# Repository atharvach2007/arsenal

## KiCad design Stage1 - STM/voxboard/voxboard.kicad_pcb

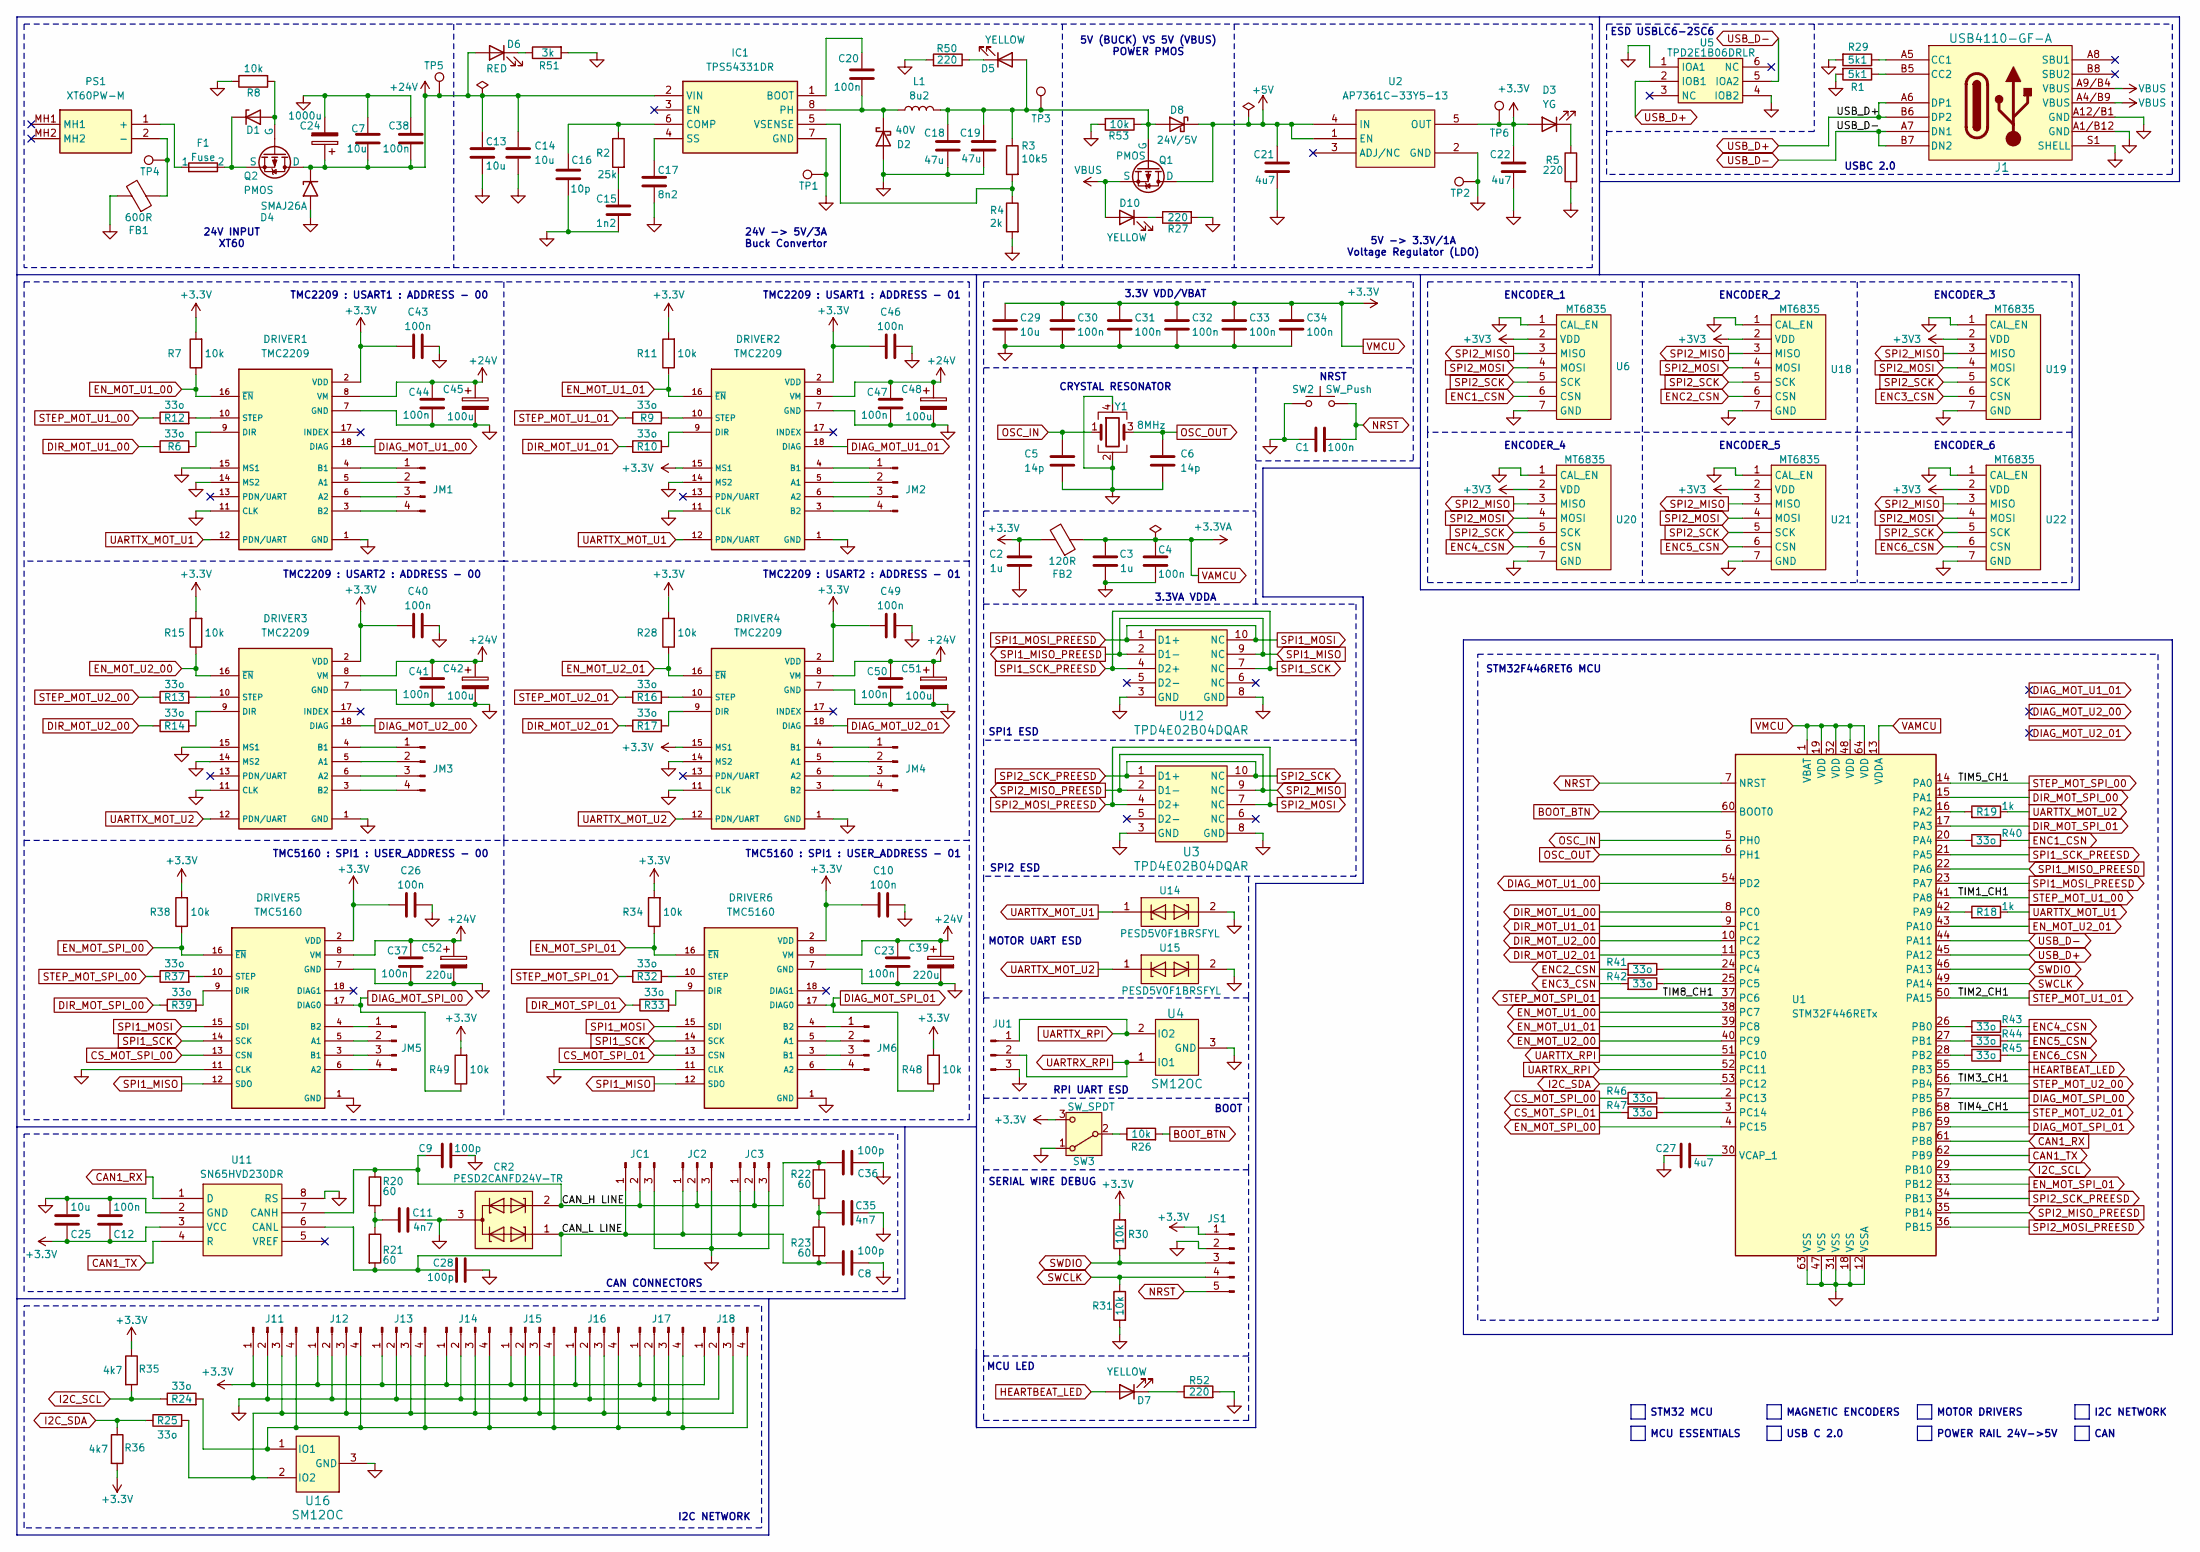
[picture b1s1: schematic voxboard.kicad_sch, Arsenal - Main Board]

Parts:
C1, C4, C10, C12, C23, C26, C30, C31, C32, C33, C34, C37, C38, C40, C41, C43, C44, C46, C47, C49, C50: 100n; C_0402_1005Metric
C2, C3: 1u; C_0603_1608Metric
C5, C6: 14p; C_0402_1005Metric
C7, C25, C29: 10u; C_0603_1608Metric
C8, C9, C28, C36: 100p; C_0402_1005Metric
C11, C35: 4n7; C_0402_1005Metric
C13, C14: 10u; C_1210_3225Metric
C15: 1n2; C_0805_2012Metric
C16: 10p; C_0805_2012Metric
C17: 8n2; C_0201_0603Metric
C18, C19: 47u; C_1210_3225Metric
C20: 100n; C_0805_2012Metric
C21, C22, C27: 4u7; C_0603_1608Metric
C24: 1000u; CP_Radial_D8.0mm_P3.50mm
C39, C52: 220u; CP_Radial_D10.0mm_P5.00mm
C42, C45, C48, C51: 100u; CP_Radial_D8.0mm_P3.50mm
CR2: PESD2CANFD24V-TR; SOT-23
D1: D_Zener; D_SOD-123
D2: 40V; D_SMA
D3: YG; LED_0603_1608Metric
D4: SMAJ26A; D_SMA
D5, D10: YELLOW; LED_0603_1608Metric
D6: RED; LED_0603_1608Metric
D7: YELLOW; LED_0805_2012Metric
D8: 24V/5V; D_SMC
DRIVER1, DRIVER2, DRIVER3, DRIVER4: TMC2209; MODULE_TMC2209_5160
DRIVER5, DRIVER6: TMC5160; MODULE_TMC2209_5160
F1: Fuse; CONN_3557-2_KEY
FB1: 600R; L_1210_3225Metric
FB2: 120R; L_0603_1608Metric
IC1: TPS54331DR; SOIC-8_3.9x4.9mm_P1.27mm
J1: USB4110-GF-A; USB_C_Receptacle_GCT_USB4110
J11, J12, J13, J14, J15, J16, J17, J18: Conn_01x04_Pin; JST_GH_BM04B-GHS-TBT_1x04-1MP_P1.25mm_Vertical
JC1, JC2, JC3: Conn_01x03_Pin; JST_GH_BM03B-GHS-TBT_1x03-1MP_P1.25mm_Vertical
JM1, JM2, JM3, JM4, JM5, JM6: Conn_01x04_Pin; JST_VH_B4P-VH-FB-B_1x04_P3.96mm_Vertical
JS1: Conn_01x05_Pin; PinHeader_1x05_P2.54mm_Vertical
JU1: Conn_01x03_Pin; PinHeader_1x03_P2.54mm_Vertical
L1: 8u2; L_KOHERELEC_MDA7050_7.3x6.6mm
PS1: XT60PW-M; AMASS_XT60PW-M_1x02_P7.20mm_Horizontal
Q1: PMOS; SOT-23
Q2: PMOS; TO-252-2
R1, R29: 5k1; R_0402_1005Metric
R2: 25k; R_0402_1005Metric
R3: 10k5; R_0402_1005Metric
R4: 2k; R_0402_1005Metric
R5, R27, R50, R52: 220; R_0402_1005Metric
R6, R9, R10, R12, R13, R14, R16, R17, R24, R25, R32, R33, R37, R39, R40, R41, R42, R43, R44, R45, R46, R47: 33o; R_0402_1005Metric
R7, R8, R11, R15, R26, R28, R30, R31, R34, R38, R48, R49, R53: 10k; R_0402_1005Metric
R18, R19: 1k; R_0402_1005Metric
R20, R21, R22, R23: 60; R_0603_1608Metric
R35, R36: 4k7; R_0402_1005Metric
R51: 3k; R_0402_1005Metric
SW2: SW_Push; SW_PUSH_B3U-1000PM
SW3: SW_SPDT; SW_SPDT_PCM12
TP1, TP2, TP4: TestPoint; TestPoint_Pad_2.0x2.0mm
TP3, TP5, TP6: TestPoint; TestPoint_Pad_D2.0mm
U1: STM32F446RETx; LQFP64-10x10mm
U2: AP7361C-33Y5-13; AP7361C-33Y5-13_SOT89-5_DIO
U3, U12: TPD4E02B04DQAR; USON-10_2.5x1.0mm_P0.5mm
U4, U16: SM12OC; SOT-23
U5: TPD2E1B06DRLR; SOT-666
U6, U18, U19, U20, U21, U22: MT6835; JST_GH_BM07B-GHS-TBT_1x07-1MP_P1.25mm_Vertical
U11: SN65HVD230DR; SOIC-8_3.9x4.9mm_P1.27mm
U14, U15: PESD5V0F1BRSFYL; Nexperia_DSN0603-2_0.6x0.3mm_P0.4mm
Y1: 8MHz; Crystal_SMD_3225-4Pin_3.2x2.5mm

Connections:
+3V3: U6.2 (VDD), U18.2 (VDD), U19.2 (VDD), U20.2 (VDD), U21.2 (VDD), U22.2 (VDD)
+5V: C21.1, D8.1 (K), Q1.1 (D), U2.1 (EN), U2.4 (IN)
+24V: C7.2, C13.1, C14.1, C23.1, C24.1, C37.1, C38.2, C39.1, C41.1, C42.1, C44.1, C45.1, C47.1, C48.1, C50.1, C51.1, C52.1, D4.1 (A1), D6.2 (A), DRIVER1.8 (VM), DRIVER2.8 (VM), DRIVER3.8 (VM), DRIVER4.8 (VM), DRIVER5.8 (VM), DRIVER6.8 (VM), IC1.2 (VIN), Q2.1 (D), TP5.1
/CAN_H LINE: C9.1, C36.1, CR2.2, JC1.2, JC2.2, JC3.2, R20.1, R22.1, U11.7 (CANH)
/CAN_L LINE: C8.1, C28.1, CR2.1, JC1.1, JC2.1, JC3.1, R21.2, R23.2, U11.6 (CANL)
BOOT_BTN: R26.2, U1.60 (BOOT0)
CAN1_RX: U1.61 (PB8), U11.1 (D)
CAN1_TX: U1.62 (PB9), U11.4 (R)
CS_MOT_SPI_00: DRIVER5.13 (CSN), R46.2
CS_MOT_SPI_01: DRIVER6.13 (CSN), R47.2
DIAG_MOT_SPI_00: DRIVER5.17 (DIAG0), R49.1, U1.57 (PB5)
DIAG_MOT_SPI_01: DRIVER6.17 (DIAG0), R48.1, U1.59 (PB7)
DIAG_MOT_U1_00: DRIVER1.18 (DIAG), U1.54 (PD2)
DIAG_MOT_U1_01: DRIVER2.18 (DIAG)
DIAG_MOT_U2_00: DRIVER3.18 (DIAG)
DIAG_MOT_U2_01: DRIVER4.18 (DIAG)
DIR_MOT_SPI_00: R39.1, U1.15 (PA1)
DIR_MOT_SPI_01: R33.1, U1.17 (PA3)
DIR_MOT_U1_00: R6.1, U1.8 (PC0)
DIR_MOT_U1_01: R10.1, U1.9 (PC1)
DIR_MOT_U2_00: R14.1, U1.10 (PC2)
DIR_MOT_U2_01: R17.1, U1.11 (PC3)
ENC1_CSN: R40.2, U6.6 (CSN)
ENC2_CSN: R41.2, U18.6 (CSN)
ENC3_CSN: R42.2, U19.6 (CSN)
ENC4_CSN: R43.2, U20.6 (CSN)
ENC5_CSN: R44.2, U21.6 (CSN)
ENC6_CSN: R45.2, U22.6 (CSN)
EN_MOT_SPI_00: DRIVER5.16 (~EN), R38.1, U1.4 (PC15)
EN_MOT_SPI_01: DRIVER6.16 (~EN), R34.1, U1.33 (PB12)
EN_MOT_U1_00: DRIVER1.16 (~EN), R7.1, U1.38 (PC7)
EN_MOT_U1_01: DRIVER2.16 (~EN), R11.1, U1.39 (PC8)
EN_MOT_U2_00: DRIVER3.16 (~EN), R15.1, U1.40 (PC9)
EN_MOT_U2_01: DRIVER4.16 (~EN), R28.1, U1.43 (PA10)
GND: C1.1, C2.2, C3.2, C4.2, C5.2, C6.2, C7.1, C8.2, C9.2, C10.2, C11.2, C12.2, C13.2, C14.2, C15.2, C16.2, C17.2, C18.2, C19.2, C21.2, C22.2, C23.2, C24.2, C25.2, C26.2, C27.1, C28.2, C29.2, C30.2, C31.2, C32.2, C33.2, C34.2, C35.2, C36.2, C37.2, C38.1, C39.2, C40.2, C41.2, C42.2, C43.2, C44.2, C45.2, C46.2, C47.2, C48.2, C49.2, C50.2, C51.2, C52.2, CR2.3, D2.2 (A), D4.2 (A2), DRIVER1.1 (GND), DRIVER1.7 (GND), DRIVER1.11 (CLK), DRIVER1.14 (MS2), DRIVER1.15 (MS1), DRIVER2.1 (GND), DRIVER2.7 (GND), DRIVER2.11 (CLK), DRIVER2.14 (MS2), DRIVER3.1 (GND), DRIVER3.7 (GND), DRIVER3.11 (CLK), DRIVER3.14 (MS2), DRIVER3.15 (MS1), DRIVER4.1 (GND), DRIVER4.7 (GND), DRIVER4.11 (CLK), DRIVER4.14 (MS2), DRIVER5.1 (GND), DRIVER5.7 (GND), DRIVER5.11 (CLK), DRIVER6.1 (GND), DRIVER6.7 (GND), DRIVER6.11 (CLK), FB1.2, IC1.7 (GND), J1.A1/B12 (GND), J1.A12/B1 (GND), J1.S1 (SHELL), J11.2, J12.2, J13.2, J14.2, J15.2, J16.2, J17.2, J18.2, JC1.3, JC2.3, JC3.3, JS1.2, JU1.3, R1.2, R4.2, R5.2, R8.1, R27.2, R29.2, R31.2, R50.2, R51.2, R52.2, R53.2, SW2.1, SW3.1 (A), TP1.1, TP2.1, U1.12 (VSSA), U1.18 (VSS), U1.31 (VSS), U1.47 (VSS), U1.63 (VSS), U2.2 (GND), U3.3 (GND), U3.8 (GND), U4.3 (GND), U5.1 (IOA1), U5.4 (IOB2), U6.1 (CAL_EN), U6.7 (GND), U11.2 (GND), U11.8 (RS), U12.3 (GND), U12.8 (GND), U14.2, U15.2, U16.3 (GND), U18.1 (CAL_EN), U18.7 (GND), U19.1 (CAL_EN), U19.7 (GND), U20.1 (CAL_EN), U20.7 (GND), U21.1 (CAL_EN), U21.7 (GND), U22.1 (CAL_EN), U22.7 (GND), Y1.2 (G), Y1.4 (G)
HEARTBEAT_LED: D7.2 (A), U1.55 (PB3)
I2C_SCL: R24.1, R35.2, U1.29 (PB10)
I2C_SDA: R25.1, R36.1, U1.53 (PC12)
NRST: C1.2, JS1.5, SW2.2, U1.7 (NRST)
unnamed: C11.1, R20.2, R21.1
unnamed: C15.1, R2.2
unnamed: C35.1, R22.2, R23.1
unnamed: D1.2 (A), Q2.2 (G), R8.2
unnamed: D1.1 (K), F1.2, Q2.3 (S)
unnamed: C20.2, D2.1 (K), IC1.8 (PH), L1.1
unnamed: D3.1 (K), R5.1
unnamed: C18.1, C19.1, D5.2 (A), D8.2 (A), L1.2, Q1.2 (G), R3.1, R53.1, TP3.1
unnamed: D5.1 (K), R50.1
unnamed: D6.1 (K), R51.1
unnamed: D7.1 (K), R52.1
unnamed: D10.1 (K), R27.1
unnamed: DRIVER1.5 (A1), JM1.2
unnamed: DRIVER1.6 (A2), JM1.3
unnamed: DRIVER1.4 (B1), JM1.1
unnamed: DRIVER1.3 (B2), JM1.4
unnamed: DRIVER1.9 (DIR), R6.2
unnamed: DRIVER1.10 (STEP), R12.2
unnamed: DRIVER2.5 (A1), JM2.2
unnamed: DRIVER2.6 (A2), JM2.3
unnamed: DRIVER2.4 (B1), JM2.1
unnamed: DRIVER2.3 (B2), JM2.4
unnamed: DRIVER2.9 (DIR), R10.2
unnamed: DRIVER2.10 (STEP), R9.2
unnamed: DRIVER3.5 (A1), JM3.2
unnamed: DRIVER3.6 (A2), JM3.3
unnamed: DRIVER3.4 (B1), JM3.1
unnamed: DRIVER3.3 (B2), JM3.4
unnamed: DRIVER3.9 (DIR), R14.2
unnamed: DRIVER3.10 (STEP), R13.2
unnamed: DRIVER4.5 (A1), JM4.2
unnamed: DRIVER4.6 (A2), JM4.3
unnamed: DRIVER4.4 (B1), JM4.1
unnamed: DRIVER4.3 (B2), JM4.4
unnamed: DRIVER4.9 (DIR), R17.2
unnamed: DRIVER4.10 (STEP), R16.2
unnamed: DRIVER5.5 (A1), JM5.2
unnamed: DRIVER5.6 (A2), JM5.4
unnamed: DRIVER5.3 (B1), JM5.3
unnamed: DRIVER5.4 (B2), JM5.1
unnamed: DRIVER5.9 (DIR), R39.2
unnamed: DRIVER5.10 (STEP), R37.2
unnamed: DRIVER6.5 (A1), JM6.2
unnamed: DRIVER6.6 (A2), JM6.4
unnamed: DRIVER6.3 (B1), JM6.3
unnamed: DRIVER6.4 (B2), JM6.1
unnamed: DRIVER6.9 (DIR), R33.2
unnamed: DRIVER6.10 (STEP), R32.2
unnamed: C20.1, IC1.1 (BOOT)
unnamed: C16.1, IC1.6 (COMP), R2.1
unnamed: C17.1, IC1.4 (SS)
unnamed: IC1.5 (VSENSE), R3.2, R4.1
unnamed: J1.A5 (CC1), R29.1
unnamed: J1.B5 (CC2), R1.1
unnamed: J11.3, J12.3, J13.3, J14.3, J15.3, J16.3, J17.3, J18.3, R25.2, U16.2 (IO2)
unnamed: J11.4, J12.4, J13.4, J14.4, J15.4, J16.4, J17.4, J18.4, R24.2, U16.1 (IO1)
unnamed: F1.1, PS1.1 (+)
unnamed: FB1.1, PS1.2 (-), TP4.1
unnamed: R26.1, SW3.2 (B)
unnamed: R19.2, U1.16 (PA2)
unnamed: R40.1, U1.20 (PA4)
unnamed: R18.2, U1.42 (PA9)
unnamed: R43.1, U1.26 (PB0)
unnamed: R44.1, U1.27 (PB1)
unnamed: R45.1, U1.28 (PB2)
unnamed: R41.1, U1.24 (PC4)
unnamed: R42.1, U1.25 (PC5)
unnamed: R46.1, U1.2 (PC13)
unnamed: R47.1, U1.3 (PC14)
unnamed: C27.2, U1.30 (VCAP_1)
OSC_IN: C5.1, U1.5 (PH0), Y1.1
OSC_OUT: C6.1, U1.6 (PH1), Y1.3
SPI1_MISO: DRIVER5.12 (SDO), DRIVER6.12 (SDO), U1.22 (PA6), U12.2 (D1-), U12.9 (NC)
SPI1_MOSI: DRIVER5.15 (SDI), DRIVER6.15 (SDI), U1.23 (PA7), U12.1 (D1+), U12.10 (NC)
SPI1_SCK: DRIVER5.14 (SCK), DRIVER6.14 (SCK), U1.21 (PA5), U12.4 (D2+), U12.7 (NC)
SPI2_MISO: U1.35 (PB14), U3.2 (D1-), U3.9 (NC), U6.3 (MISO), U18.3 (MISO), U19.3 (MISO), U20.3 (MISO), U21.3 (MISO), U22.3 (MISO)
SPI2_MOSI: U1.36 (PB15), U3.4 (D2+), U3.7 (NC), U6.4 (MOSI), U18.4 (MOSI), U19.4 (MOSI), U20.4 (MOSI), U21.4 (MOSI), U22.4 (MOSI)
SPI2_SCK: U1.34 (PB13), U3.1 (D1+), U3.10 (NC), U6.5 (SCK), U18.5 (SCK), U19.5 (SCK), U20.5 (SCK), U21.5 (SCK), U22.5 (SCK)
STEP_MOT_SPI_00: R37.1, U1.14 (PA0)
STEP_MOT_SPI_01: R32.1, U1.37 (PC6)
STEP_MOT_U1_00: R12.1, U1.41 (PA8)
STEP_MOT_U1_01: R9.1, U1.50 (PA15)
STEP_MOT_U2_00: R13.1, U1.56 (PB4)
STEP_MOT_U2_01: R16.1, U1.58 (PB6)
SWCLK: JS1.4, R31.1, U1.49 (PA14)
SWDIO: JS1.3, R30.1, U1.46 (PA13)
UARTRX_RPI: JU1.2, U1.52 (PC11), U4.1 (IO1)
UARTTX_MOT_U1: DRIVER1.12 (PDN/UART), DRIVER2.12 (PDN/UART), R18.1, U14.1
UARTTX_MOT_U2: DRIVER3.12 (PDN/UART), DRIVER4.12 (PDN/UART), R19.1, U15.1
UARTTX_RPI: JU1.1, U1.51 (PC10), U4.2 (IO2)
USB_D+: J1.A6 (DP1), J1.B6 (DP2), U1.45 (PA12), U5.2 (IOB1)
USB_D-: J1.A7 (DN1), J1.B7 (DN2), U1.44 (PA11), U5.5 (IOA2)
VAMCU: C3.1, C4.1, FB2.1, U1.13 (VDDA)
VBUS: D10.2 (A), J1.A4/B9 (VBUS), J1.A9/B4 (VBUS), Q1.3 (S)
VMCU: C2.1, C10.1, C12.1, C22.1, C25.1, C26.1, C29.1, C30.1, C31.1, C32.1, C33.1, C34.1, C40.1, C43.1, C46.1, C49.1, D3.2 (A), DRIVER1.2 (VDD), DRIVER2.2 (VDD), DRIVER2.15 (MS1), DRIVER3.2 (VDD), DRIVER4.2 (VDD), DRIVER4.15 (MS1), DRIVER5.2 (VDD), DRIVER6.2 (VDD), FB2.2, J11.1, J12.1, J13.1, J14.1, J15.1, J16.1, J17.1, J18.1, JS1.1, R7.2, R11.2, R15.2, R28.2, R30.2, R34.2, R35.1, R36.2, R38.2, R48.2, R49.2, SW3.3 (C), TP6.1, U1.1 (VBAT), U1.19 (VDD), U1.32 (VDD), U1.48 (VDD), U1.64 (VDD), U2.5 (OUT), U11.3 (VCC)

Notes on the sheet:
ESD USBLC6-2SC6
STM32 MCU
NRST
TMC5160 : SPI1 : USER_ADDRESS - 01
ENCODER_4
MOTOR UART ESD
TMC2209 : USART2 : ADDRESS - 00
TMC2209 : USART1 : ADDRESS - 01
ENCODER_6
MOTOR DRIVERS
BOOT
MAGNETIC ENCODERS
RPI UART ESD
3.3V VDD/VBAT
CAN
TMC2209 : USART2 : ADDRESS - 01
TMC5160 : SPI1 : USER_ADDRESS - 00
ENCODER_5
CAN CONNECTORS
SPI1 ESD
USBC 2.0
I2C NETWORK
MCU ESSENTIALS
3.3VA VDDA
ENCODER_2
24V -> 5V/3A Buck Convertor
SPI2 ESD
ENCODER_3
USB C 2.0
MCU LED
POWER RAIL 24V->5V
CRYSTAL RESONATOR
SERIAL WIRE DEBUG
STM32F446RET6 MCU
5V -> 3.3V/1A Voltage Regulator (LDO)
TMC2209 : USART1 : ADDRESS - 00
ENCODER_1
24V INPUT XT60
5V (BUCK) VS 5V (VBUS) POWER PMOS

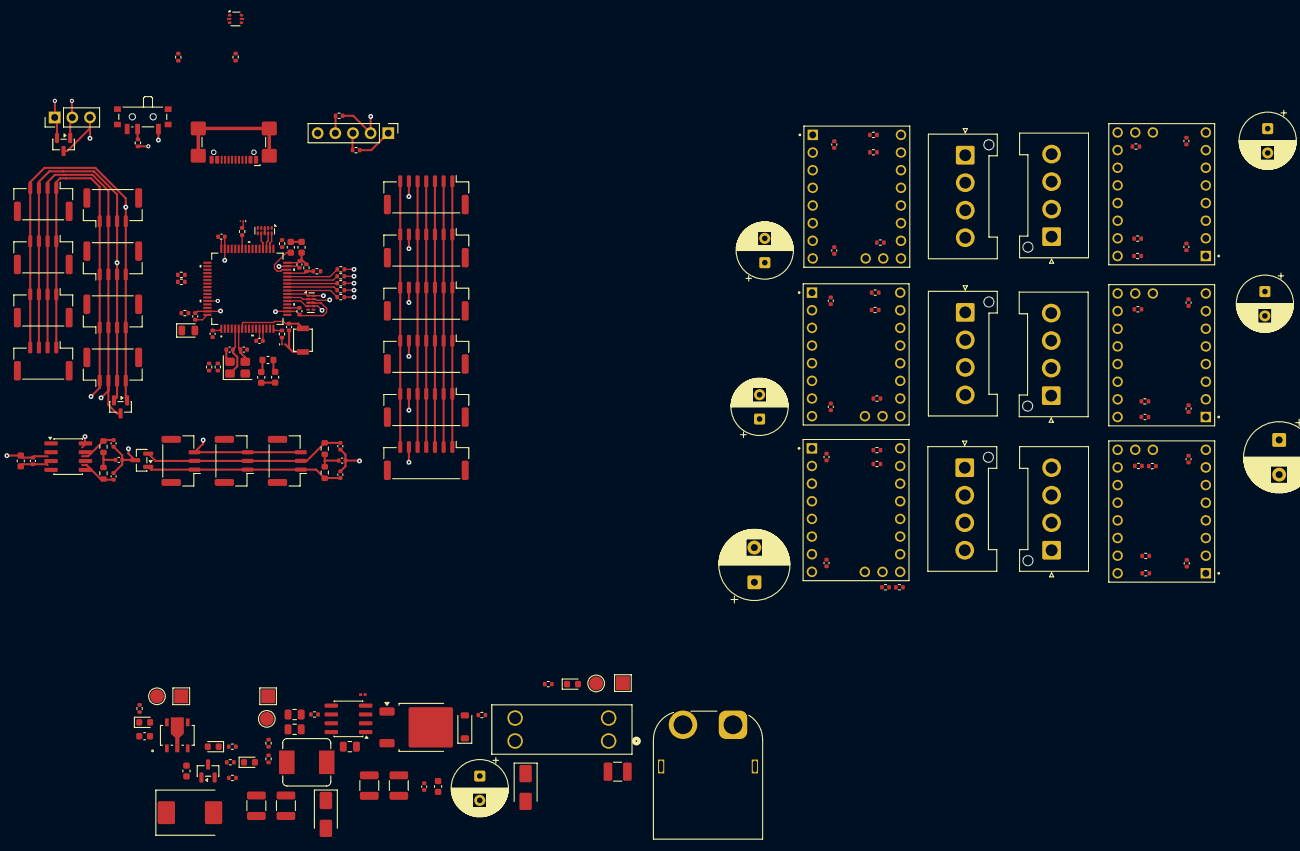
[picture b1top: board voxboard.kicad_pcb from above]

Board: 4 copper layers, 174 parts (0 on the bottom side), 131 nets.

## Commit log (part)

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2026-05-29 KICAD PROJ
2026-06-28 Assets

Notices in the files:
Stage1 - STM/voxboard/voxboard.kicad_sch:
Copyright © 2026 Atharva Chauhan. All rights reserved.
